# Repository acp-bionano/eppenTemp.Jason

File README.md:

Eppendorf-sized Temperature Sensor
=========
by Andrew Payne and Charles Fracchia

We created a networked temperature sensor that is designed to have the same lower footprint as an eppendorf tube. These sensors are designed to allow the continuous collection of sample temperature in molecular biology experiments.
It is designed to interface with the [Protocol Descriptor Language]() web-system and provide quantifiable information about temperature variability in your protocols.

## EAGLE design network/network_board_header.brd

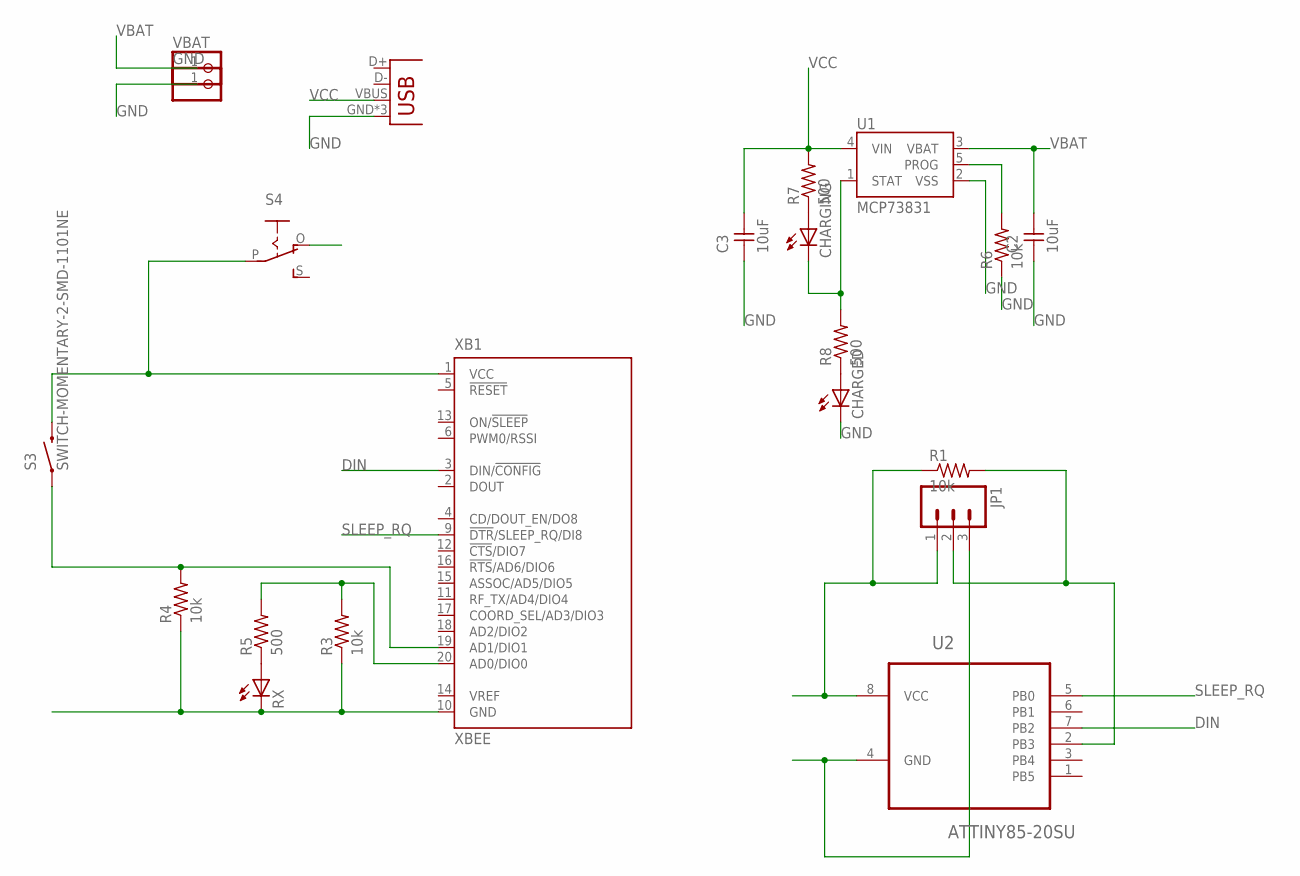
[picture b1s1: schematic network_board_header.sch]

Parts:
C2, C3: 10uF; 1206
CHARGED: LED1206; 1206
CHARGING: LED1206; 1206
GND: PINHD-1X1CB; 1X01-CLEANBIG
JP1: M03PTH; 1X03
R1: 10k; 1206
R3, R4, R6: 10k; R1206
R5, R7, R8: 500; R1206
RX: LED1206; 1206
S3: SWITCH-MOMENTARY-2-SMD-1101NE; TACTILE-SWITCH-1101NE
S4: EG1218S; EG1218
U1: MCP73831; SOT23-5
U2: ATTINY85-20SU; SOIC127P798X216-8N
VBAT: PINHD-1X1CB; 1X01-CLEANBIG
X1: USB-MICROB
XB1: XBEE

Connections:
DIN: U2.7 (PB2), XB1.3 (DIN/!CONFIG)
GND: C2.1, C3.1, CHARGED.2 (C), GND.1, JP1.3, R3.1, R4.1, R6.1, RX.2 (C), U1.2 (VSS), U2.4 (GND), X1.GND, X1.MT1 (GND), X1.MT2 (GND), XB1.10 (GND)
unnamed: R4.2, S3.P$1 (1), XB1.19 (AD1/DIO1)
unnamed: R5.1, RX.1 (A)
unnamed: R3.2, R5.2, XB1.20 (AD0/DIO0)
unnamed: R6.2, U1.5 (PROG)
unnamed: CHARGING.1 (A), R7.1
unnamed: CHARGED.1 (A), R8.1
unnamed: CHARGING.2 (C), R8.2, U1.1 (STAT)
unnamed: JP1.2, R1.2, U2.2 (PB3)
SLEEP_RQ: U2.5 (PB0), XB1.9 (!DTR!/SLEEP_RQ/DI8)
VBAT: C2.2, S4.O, U1.3 (VBAT), VBAT.1
VCC: C3.2, R7.2, U1.4 (VIN), X1.VBUS
VIN: JP1.1, R1.1, S3.P$2 (2), S4.P, U2.8 (VCC), XB1.1 (VCC)

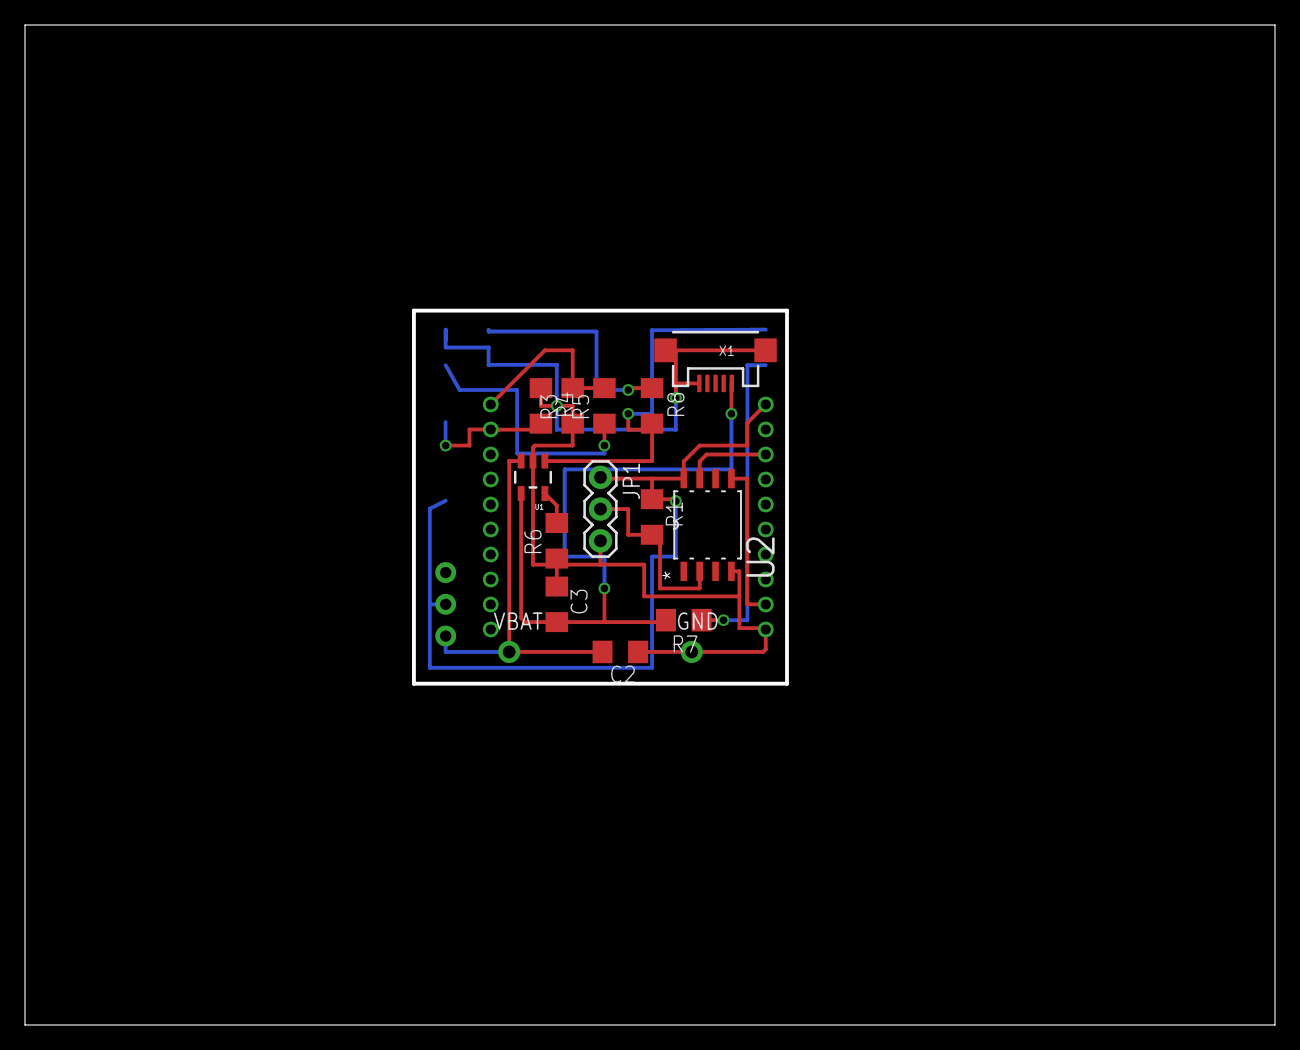
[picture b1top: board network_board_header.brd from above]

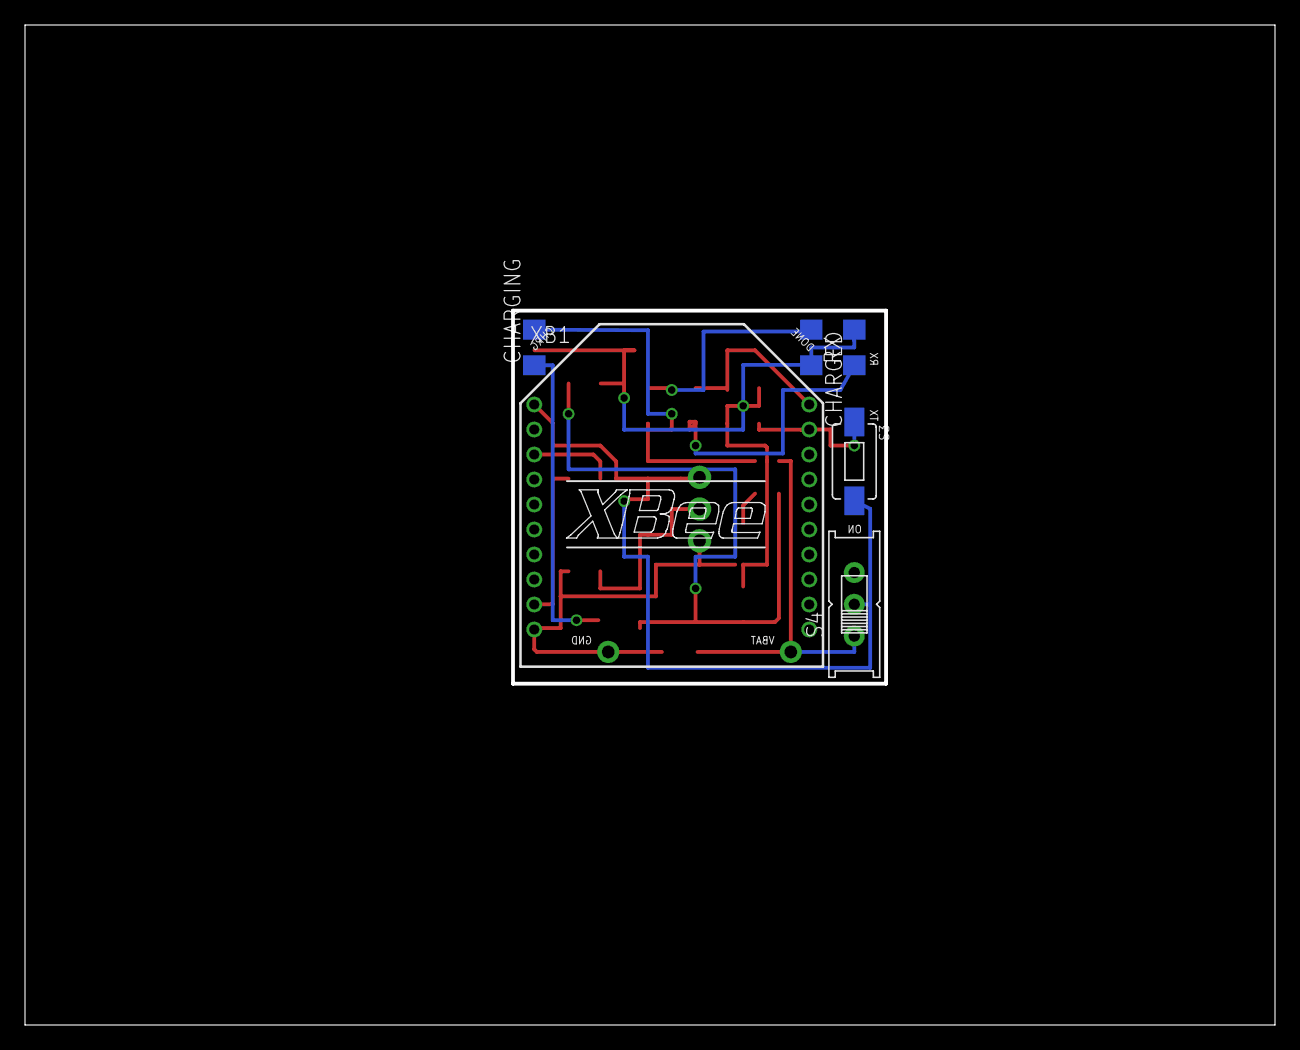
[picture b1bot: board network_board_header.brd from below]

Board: 2 copper layers, 100.0 x 80.0 mm, 21 parts (6 on the bottom side), 14 nets.

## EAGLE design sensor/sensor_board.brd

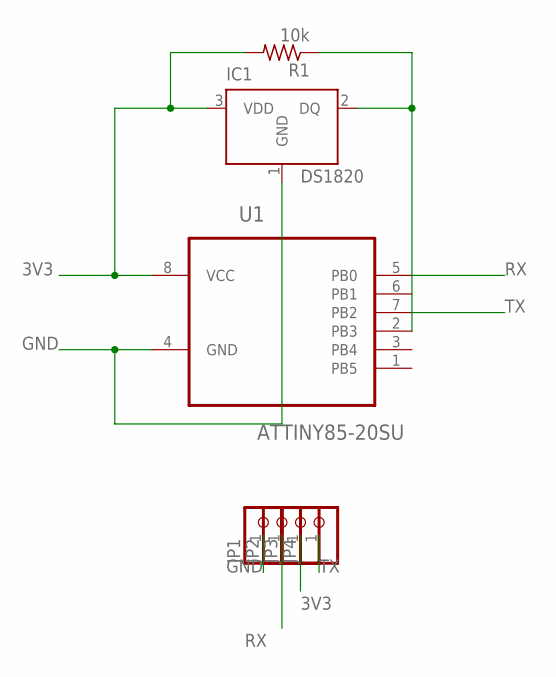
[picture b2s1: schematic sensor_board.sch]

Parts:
IC1: DS1820; TO-92
JP1, JP2, JP3, JP4: PINHD-1X1; 1X01
R1: 10k; R1206
U1: ATTINY85-20SU; SOIC127P798X216-8N

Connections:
3V3: IC1.3 (VDD), JP3.1, R1.2, U1.8 (VCC)
GND: IC1.1 (GND), JP1.1, U1.4 (GND)
unnamed: IC1.2 (DQ), R1.1, U1.2 (PB3)
RX: JP2.1, U1.5 (PB0)
TX: JP4.1, U1.7 (PB2)

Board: 2 copper layers, 7 parts (0 on the bottom side), 5 nets, no tracks yet.

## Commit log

2014-08-11 make public

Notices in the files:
parts and their libraries:
SparkFun-Electromechanical: Licensing: Creative Commons ShareAlike 4.0 International - https://creativecommons.org/licenses/by-sa/4.0
SparkFun-Connectors: Licensing: CC v3.0 Share-Alike You are welcome to use this library for commercial purposes.
